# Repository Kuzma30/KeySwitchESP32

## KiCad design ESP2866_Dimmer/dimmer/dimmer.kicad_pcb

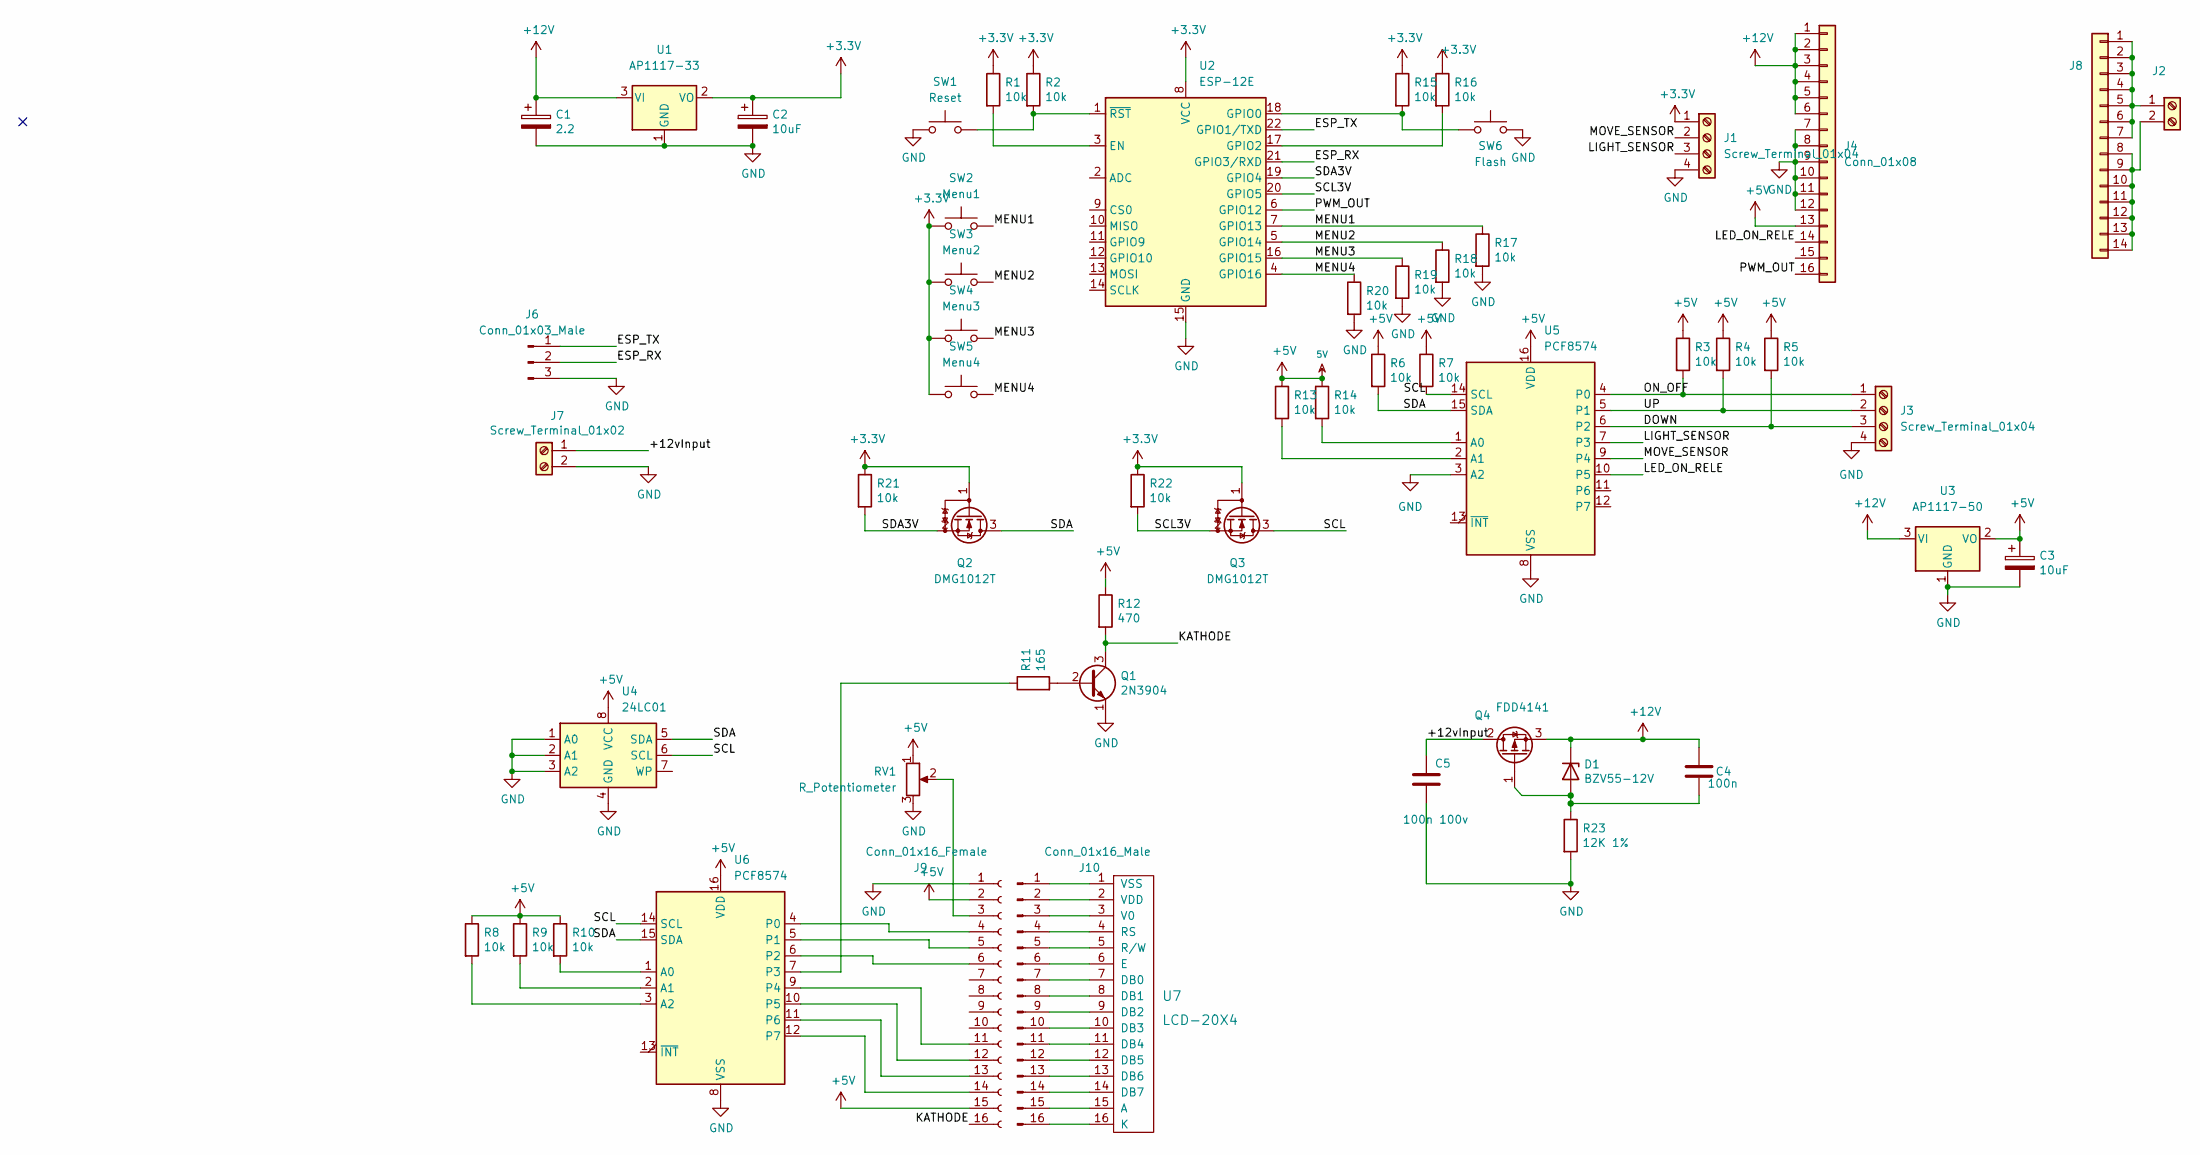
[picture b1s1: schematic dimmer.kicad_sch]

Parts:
C1: 2.2; CP_Elec_4x5.3
C2, C3: 10uF; CP_Elec_4x5.3
C4: 100n; C_1206_3216Metric_Pad1.33x1.80mm_HandSolder; Part Description 0.1uF 10% 16V Ceramic Capacitor X7R 040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
C5: 100n 100v; C_1206_3216Metric_Pad1.33x1.80mm_HandSolder; Part Description 0.1uF 10% 100V Ceramic Capacitor X5R 04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
D1: BZV55-12V; D_MiniMELF
J1: Screw_Terminal_01x04; DG126-5.0-04P-14_Vertical
J2: Screw_Terminal_01x02; DG126-5.0-02P-14_Vertical
J3: Screw_Terminal_01x04; JST_NV_B04P-NV_1x04_P5.00mm_Vertical
J4: Conn_01x08; PinSocket_1x16_P1.27mm_Vertical
J6: Conn_01x03_Male; JST_EH_B3B-EH-A_1x03_P2.50mm_Vertical
J7: Screw_Terminal_01x02; JST_NV_B02P-NV_1x02_P5.00mm_Vertical
J8: Conn_01x06; PinSocket_1x14_P1.27mm_Vertical
J9: Conn_01x16_Female; PinSocket_1x16_P2.54mm_Vertical
J10: Conn_01x16_Male
Q1: 2N3904; TO-92_Inline
Q2, Q3: DMG1012T; SOT-523
Q4: FDD4141; DPAK-3
R1, R2, R3, R4, R5, R6, R7, R8, R9, R10, R13, R14, R15, R16, R17, R18, R19, R20, R21, R22: 10k; R_1206_3216Metric_Pad1.30x1.75mm_HandSolder
R11: 165; R_1206_3216Metric_Pad1.30x1.75mm_HandSolder
R12: 470; R_1206_3216Metric_Pad1.30x1.75mm_HandSolder
R23: 12K 1%; R_1206_3216Metric; Part Description Resistor 12K M1005 1% 63mW
RV1: R_Potentiometer
SW1: Reset; SW_PUSH_6mm
SW2: Menu1; SW_PUSH_6mm
SW3: Menu2; SW_PUSH_6mm
SW4: Menu3; SW_PUSH_6mm
SW5: Menu4; SW_PUSH_6mm
SW6: Flash; SW_PUSH_6mm
U1: AP1117-33; SOT-223-3_TabPin2
U2: ESP-12E
U3: AP1117-50; SOT-223-3_TabPin2
U4: 24LC01; SOIC-8_3.9x4.9mm_P1.27mm
U5, U6: PCF8574; SOIC-16W_7.5x10.3mm_P1.27mm
U7: LCD-20X4

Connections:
+3V3: C2.1, J1.1, Q2.1 (G), Q3.1 (G), R1.1, R2.1, R15.1, R16.1, R21.1, R22.1, SW2.1, SW3.1, SW4.1, SW5.1, U1.2 (VO), U2.8 (VCC)
+5V: C3.1, J4.13, J9.2, J9.15, R3.1, R4.1, R5.1, R6.1, R7.1, R8.1, R9.1, R10.1, R12.1, R13.1, R14.1, RV1.1, U3.2 (VO), U4.8 (VCC), U5.16 (VDD), U6.16 (VDD)
+12V: C1.1, C4.1, D1.1 (K), J4.1, J4.2, J4.3, J4.4, J4.5, J4.6, Q4.3 (S), U1.3 (VI), U3.3 (VI)
/+12vInput: C5.1, J7.1, Q4.2 (D)
/DOWN: J3.3, R5.2, U5.6 (P2)
/ESP_RX: J6.2, U2.21 (GPIO3/RXD)
/ESP_TX: J6.1, U2.22 (GPIO1/TXD)
/KATHODE: J9.16, Q1.3 (C), R12.2
/LED_ON_RELE: J4.14, U5.10 (P5)
/LIGHT_SENSOR: J1.3, U5.7 (P3)
/MENU1: R17.1, SW2.2, U2.7 (GPIO13)
/MENU2: R18.1, SW3.2, U2.5 (GPIO14)
/MENU3: R19.1, SW4.2, U2.16 (GPIO15)
/MENU4: R20.1, SW5.2, U2.4 (GPIO16)
/MOVE_SENSOR: J1.2, U5.9 (P4)
/ON_OFF: J3.1, R3.2, U5.4 (P0)
/PWM_OUT: J4.16, U2.6 (GPIO12)
/SCL: Q3.3 (D), R7.2, U4.6 (SCL), U5.14 (SCL), U6.14 (SCL)
/SCL3V: Q3.2 (S), R22.2, U2.20 (GPIO5)
/SDA: Q2.3 (D), R6.2, U4.5 (SDA), U5.15 (SDA), U6.15 (SDA)
/SDA3V: Q2.2 (S), R21.2, U2.19 (GPIO4)
/UP: J3.2, R4.2, U5.5 (P1)
GND: C1.2, C2.2, C3.2, C5.2, J1.4, J3.4, J4.7, J4.8, J4.9, J4.10, J4.11, J4.12, J6.3, J7.2, J9.1, Q1.1 (E), R17.2, R18.2, R19.2, R20.2, R23.2, RV1.3, SW1.1, SW6.2, U1.1 (GND), U2.15 (GND), U3.1 (GND), U4.1 (A0), U4.2 (A1), U4.3 (A2), U4.4 (GND), U5.3 (A2), U5.8 (VSS), U6.8 (VSS)
unnamed: C4.2, D1.2 (A), Q4.1 (G), R23.1
unnamed: J2.1, J8.1, J8.2, J8.3, J8.4, J8.5, J8.6, J8.7
unnamed: J2.2, J8.8, J8.9, J8.10, J8.11, J8.12, J8.13, J8.14
unnamed: J9.3, RV1.2
unnamed: J9.4, U6.4 (P0)
unnamed: J9.5, U6.5 (P1)
unnamed: J9.6, U6.6 (P2)
unnamed: J9.11, U6.9 (P4)
unnamed: J9.12, U6.10 (P5)
unnamed: J9.13, U6.11 (P6)
unnamed: J9.14, U6.12 (P7)
unnamed: J10.1, U7.1 (VSS)
unnamed: J10.2, U7.2 (VDD)
unnamed: J10.3, U7.3 (V0)
unnamed: J10.4, U7.4 (RS)
unnamed: J10.5, U7.5 (R/W)
unnamed: J10.6, U7.6 (E)
unnamed: J10.7, U7.7 (DB0)
unnamed: J10.8, U7.8 (DB1)
unnamed: J10.9, U7.9 (DB2)
unnamed: J10.10, U7.10 (DB3)
unnamed: J10.11, U7.11 (DB4)
unnamed: J10.12, U7.12 (DB5)
unnamed: J10.13, U7.13 (DB6)
unnamed: J10.14, U7.14 (DB7)
unnamed: J10.15, U7.15 (A)
unnamed: J10.16, U7.16 (K)
unnamed: Q1.2 (B), R11.2
unnamed: R1.2, U2.3 (EN)
unnamed: R2.2, SW1.2, U2.1 (~RST)
unnamed: R8.2, U6.3 (A2)
unnamed: R9.2, U6.2 (A1)
unnamed: R10.2, U6.1 (A0)
unnamed: R11.1, U6.7 (P3)
unnamed: R13.2, U5.2 (A1)
unnamed: R14.2, U5.1 (A0)
unnamed: R15.2, SW6.1, U2.18 (GPIO0)
unnamed: R16.2, U2.17 (GPIO2)

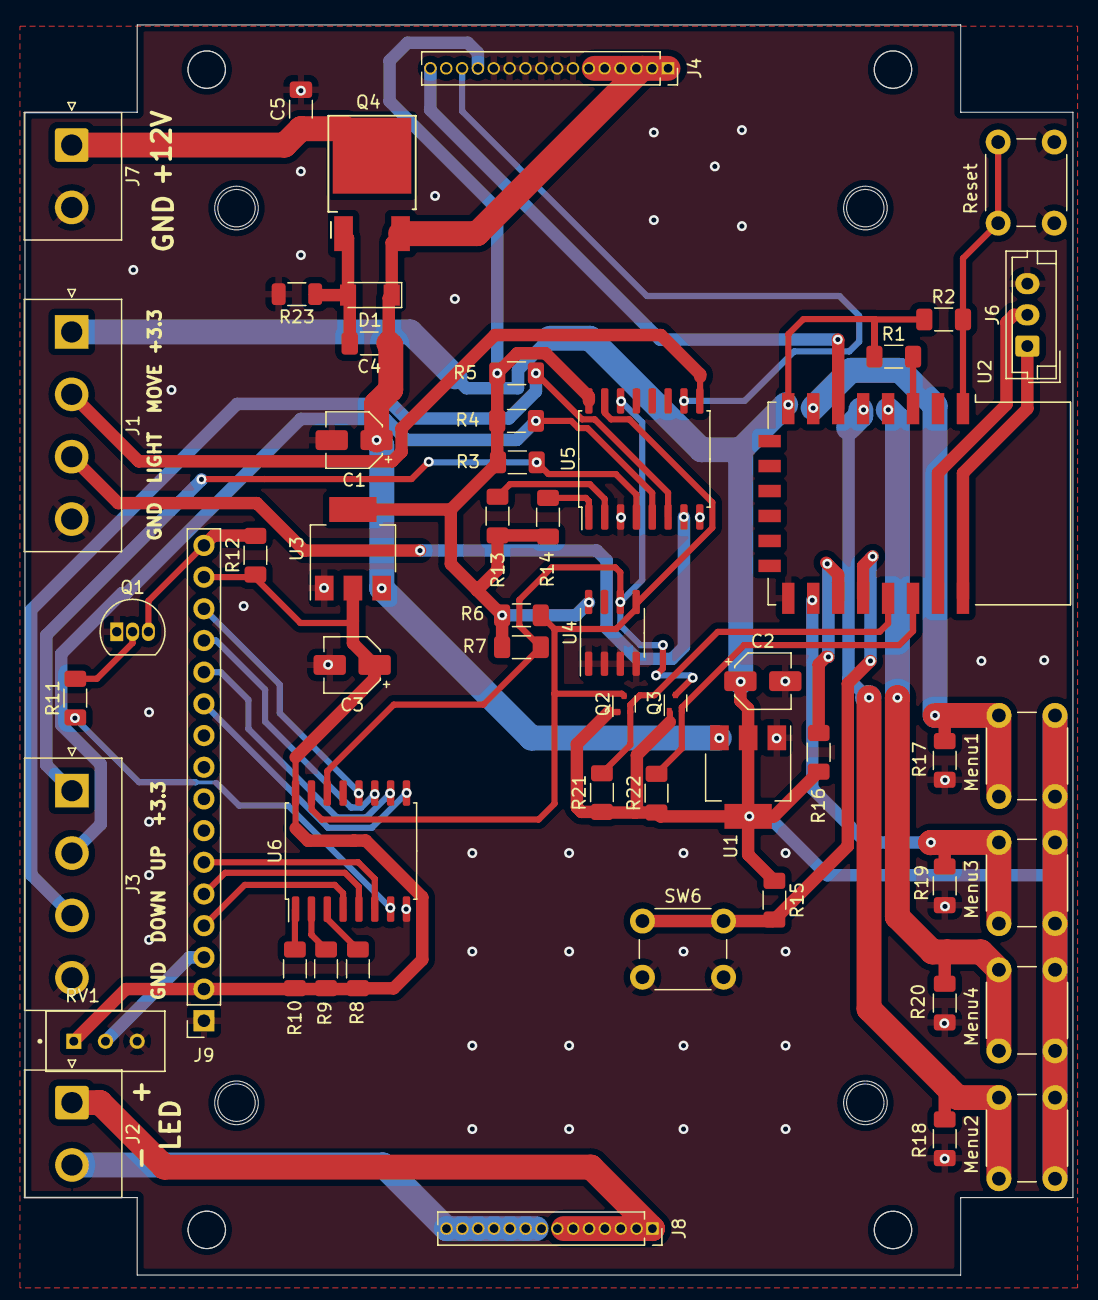
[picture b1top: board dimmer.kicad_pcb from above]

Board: 2 copper layers, 84.0 x 100.2 mm, 54 parts (0 on the bottom side), 45 nets.

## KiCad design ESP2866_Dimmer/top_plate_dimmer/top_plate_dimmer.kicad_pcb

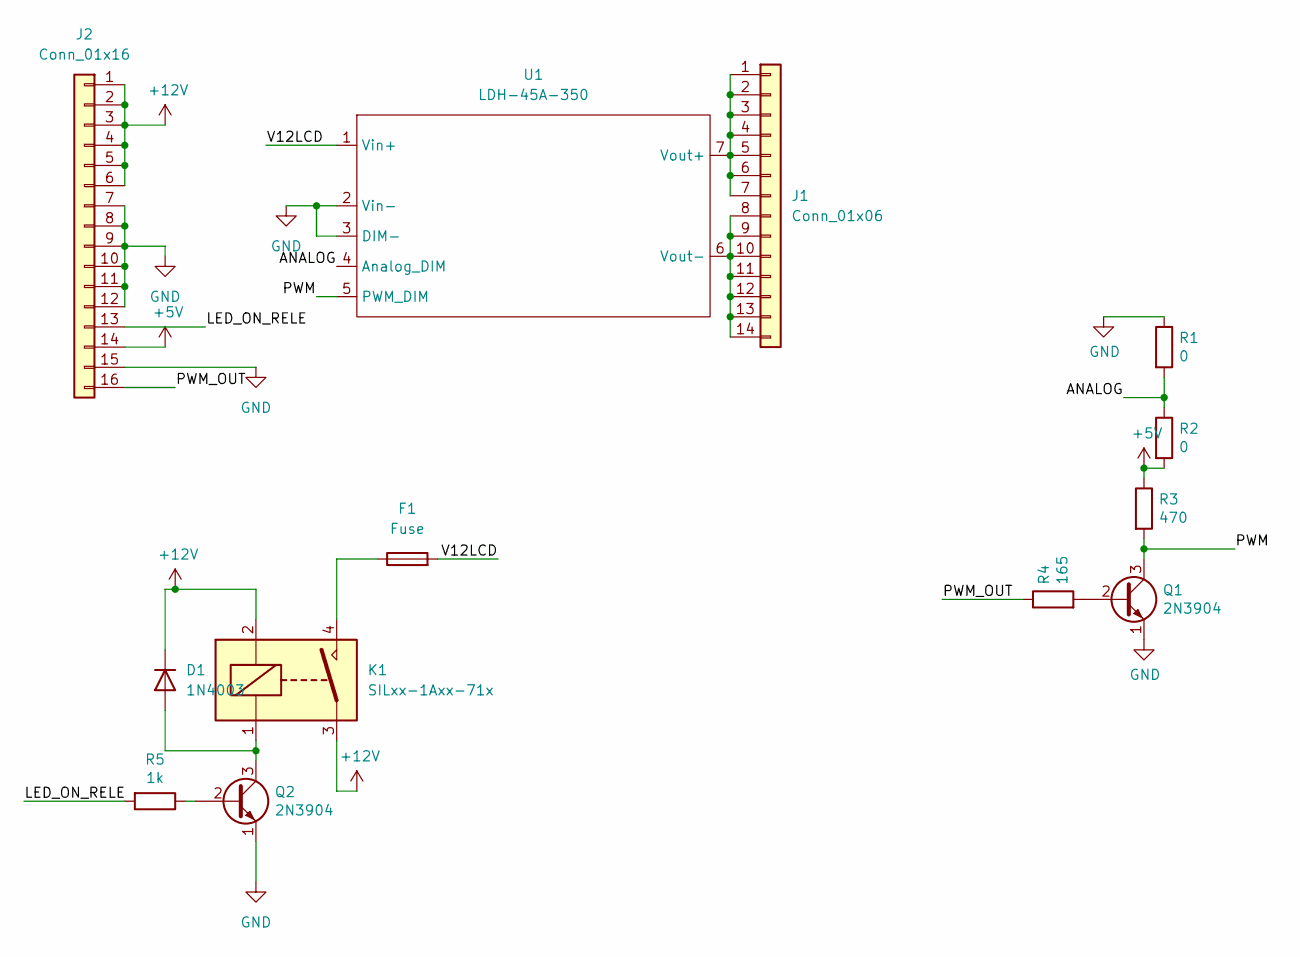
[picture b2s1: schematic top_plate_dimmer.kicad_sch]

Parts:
D1: 1N4003; D_SMA
F1: Fuse; L_Axial_L9.5mm_D4.0mm_P15.24mm_Horizontal_Fastron_SMCC
J1: Conn_01x06; PinHeader_1x14_P1.27mm_Vertical
J2: Conn_01x16; PinHeader_1x16_P1.27mm_Vertical
K1: SILxx-1Axx-71x; Realy_DPST_HF32FA
Q1, Q2: 2N3904; TO-92_Inline
R1, R2: 0; R_1206_3216Metric_Pad1.30x1.75mm_HandSolder
R3: 470; R_1206_3216Metric_Pad1.30x1.75mm_HandSolder
R4: 165; R_1206_3216Metric_Pad1.30x1.75mm_HandSolder
R5: 1k; R_1206_3216Metric_Pad1.30x1.75mm_HandSolder
U1: LDH-45A-350; LDH-45A

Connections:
+5V: J2.14, R2.2, R3.1
+12V: D1.1 (K), J2.1, J2.2, J2.3, J2.4, J2.5, J2.6, K1.2, K1.3
/ANALOG: R1.2, R2.1, U1.4 (Analog_DIM)
/LED_ON_RELE: J2.13, R5.2
/PWM: Q1.3 (C), R3.2, U1.5 (PWM_DIM)
/PWM_OUT: J2.16, R4.1
/V12LCD: F1.2, U1.1 (Vin+)
GND: J2.7, J2.8, J2.9, J2.10, J2.11, J2.12, J2.15, Q1.1 (E), Q2.1 (E), R1.1, U1.2 (Vin-), U1.3 (DIM-)
unnamed: D1.2 (A), K1.1, Q2.3 (C)
unnamed: F1.1, K1.4
unnamed: J1.1, J1.2, J1.3, J1.4, J1.5, J1.6, J1.7, U1.7 (Vout+)
unnamed: J1.8, J1.9, J1.10, J1.11, J1.12, J1.13, J1.14, U1.6 (Vout-)
unnamed: Q1.2 (B), R4.2
unnamed: Q2.2 (B), R5.1

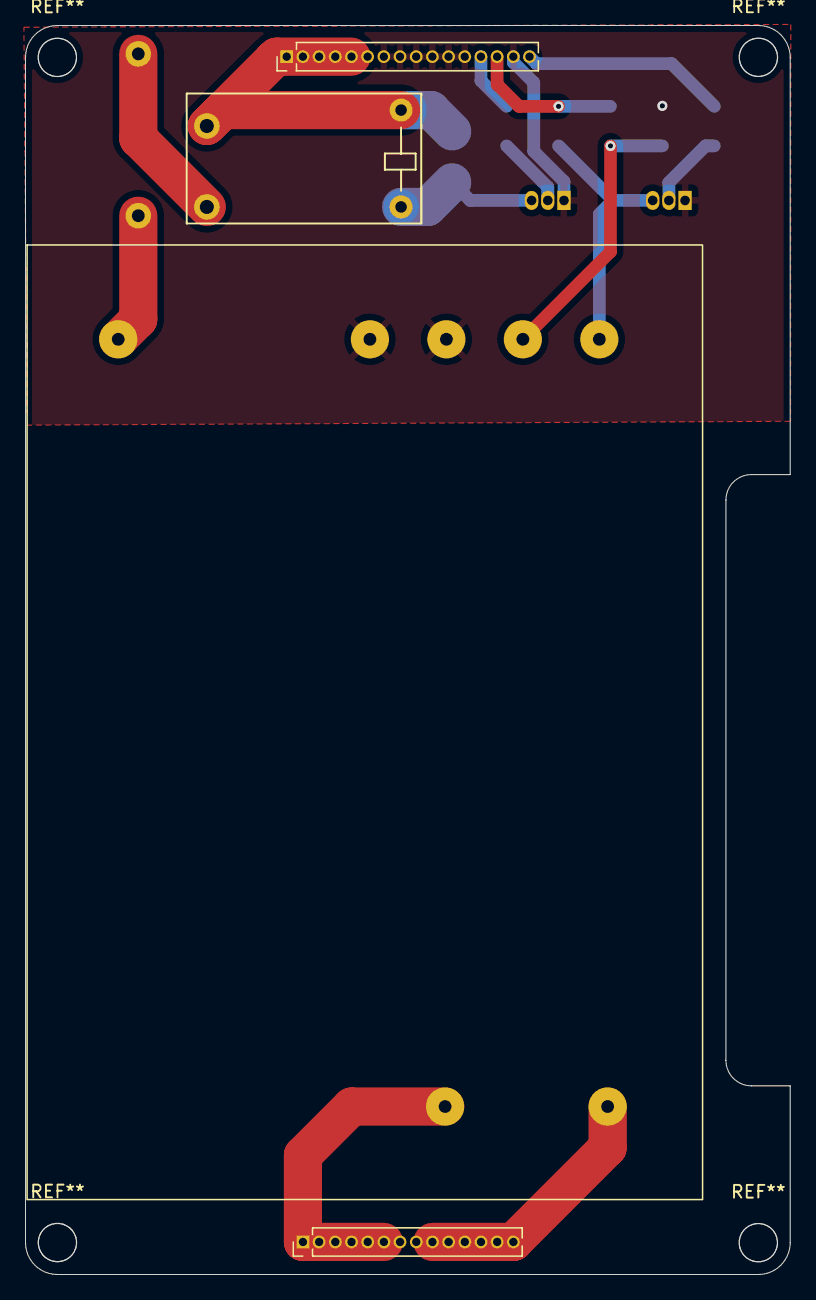
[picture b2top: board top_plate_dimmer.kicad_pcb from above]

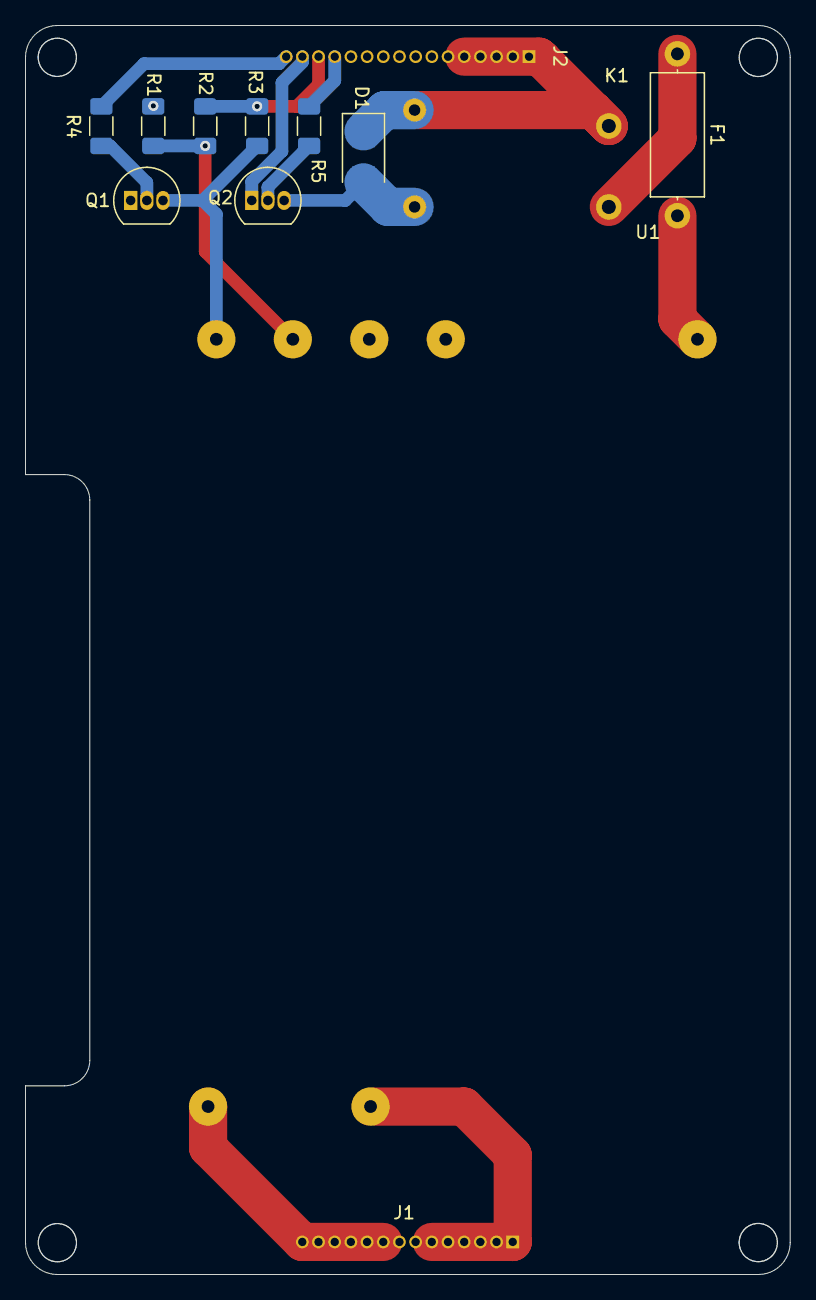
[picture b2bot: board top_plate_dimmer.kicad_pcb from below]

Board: 2 copper layers, 60.0 x 98.0 mm, 13 parts (9 on the bottom side), 14 nets.

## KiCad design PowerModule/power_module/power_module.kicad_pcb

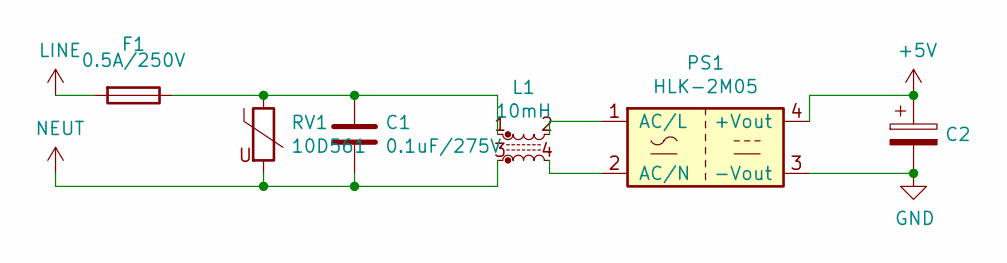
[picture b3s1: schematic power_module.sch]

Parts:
C1: 0.1uF/275V; CAP_MKP64
C2: CP; CP_Radial_D6.3mm_P2.50mm
F1: 0.5A/250V; FUZE3x10
L1: 10mH; inductor
PS1: HLK-2M05
RV1: 10D561; Varistor

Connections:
+5V: C2.1, PS1.4 (+Vout)
GND: C2.2, PS1.3 (-Vout)
LINE: F1.2
NEUT: C1.2, L1.3, RV1.2
unnamed: C1.1, F1.1, L1.1, RV1.1
unnamed: L1.2, PS1.1 (AC/L)
unnamed: L1.4, PS1.2 (AC/N)

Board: 2 copper layers, 6 parts (0 on the bottom side), 6 nets, no tracks yet.

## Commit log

2020-03-06 Initial commit
    Initial commit. (Sync with local repo)
2020-03-06 Add software file
    Add ESPHome json file for PWM single LED sensor keyswitch
2020-03-06 Add LED hole
    Добавлены карманы для верхних светодиодов подсветки. Универсально для одно/двух/трех кнопочного выключателя
2020-03-06 One Key add fasky
    Добавлена фаска к клавише
2020-12-14 Initial commit Kicad files
    Initial commit
2020-12-14 Работа над схемой. Добавлены файлы документации на реле
2021-03-28 Обновление 3Д библиотек
2022-06-09 Create esp8266.json
    not working
2022-06-10 Update esp8266.json
    Додав паочатковий код для відображення яскравості.
    Працює
    Збільшення/зменьшення яскравости кнопками
    Вмкання/вимикання лампи кнопкою
    Сенсор руху деактивовано.
2022-06-10 Update esp8266.json
    Що працює
    Початкова яскрвість при ввімкненні -30%
    Реалізовано зміну яскравості кнопками з відображення в інтерфейсі HA.
    Реалізовано ввімкнення/вимкнення світла з запамятовуванням значення яскравості.
2022-06-16 Update esp8266.json
    НІчний режим працює якщо лампа була ввімкнута паопередьно.
    Нічний режим - 30% без наявності руху. При виникненні руху - на 20 сек вмикаємо яскрвість на 90%
    Після ночі відновлення попередьої яскравості.
2022-06-22 Початкова схема діммера на esp-12
2022-06-27 Додано документацію на Wifi модуль реле. Оновлена схема та бібліотека.
2022-06-28 Оновлення схеми.
2022-06-28 Додав символ LED драйвера LDH-45A-350. Оновив схему.
2022-07-04 Оновлення схеми. Зміна типу оптрону.
2022-07-04 Фінальний варіант схеми. Початковий варінт друкованної плати.
2022-07-07 Оновлення схеми. Додано 3Д модель перетворювача.
2022-07-08 Окремий проект для плати драйверу.
2022-07-11 робота з друкованною платою
2022-07-17 Update next.
2022-07-17 Update gitignore
2022-07-25 Update board outline
2022-09-02 Big Update.
2022-09-04 Next update
2022-09-04 Add updated lib files
2022-09-29 Beta version
2022-10-01 Beta version (fixed)
2022-11-21 Beta2
2022-11-21 Beta_2
2022-11-26 Fix eeror in connection
2022-11-29 Fix error in external net
